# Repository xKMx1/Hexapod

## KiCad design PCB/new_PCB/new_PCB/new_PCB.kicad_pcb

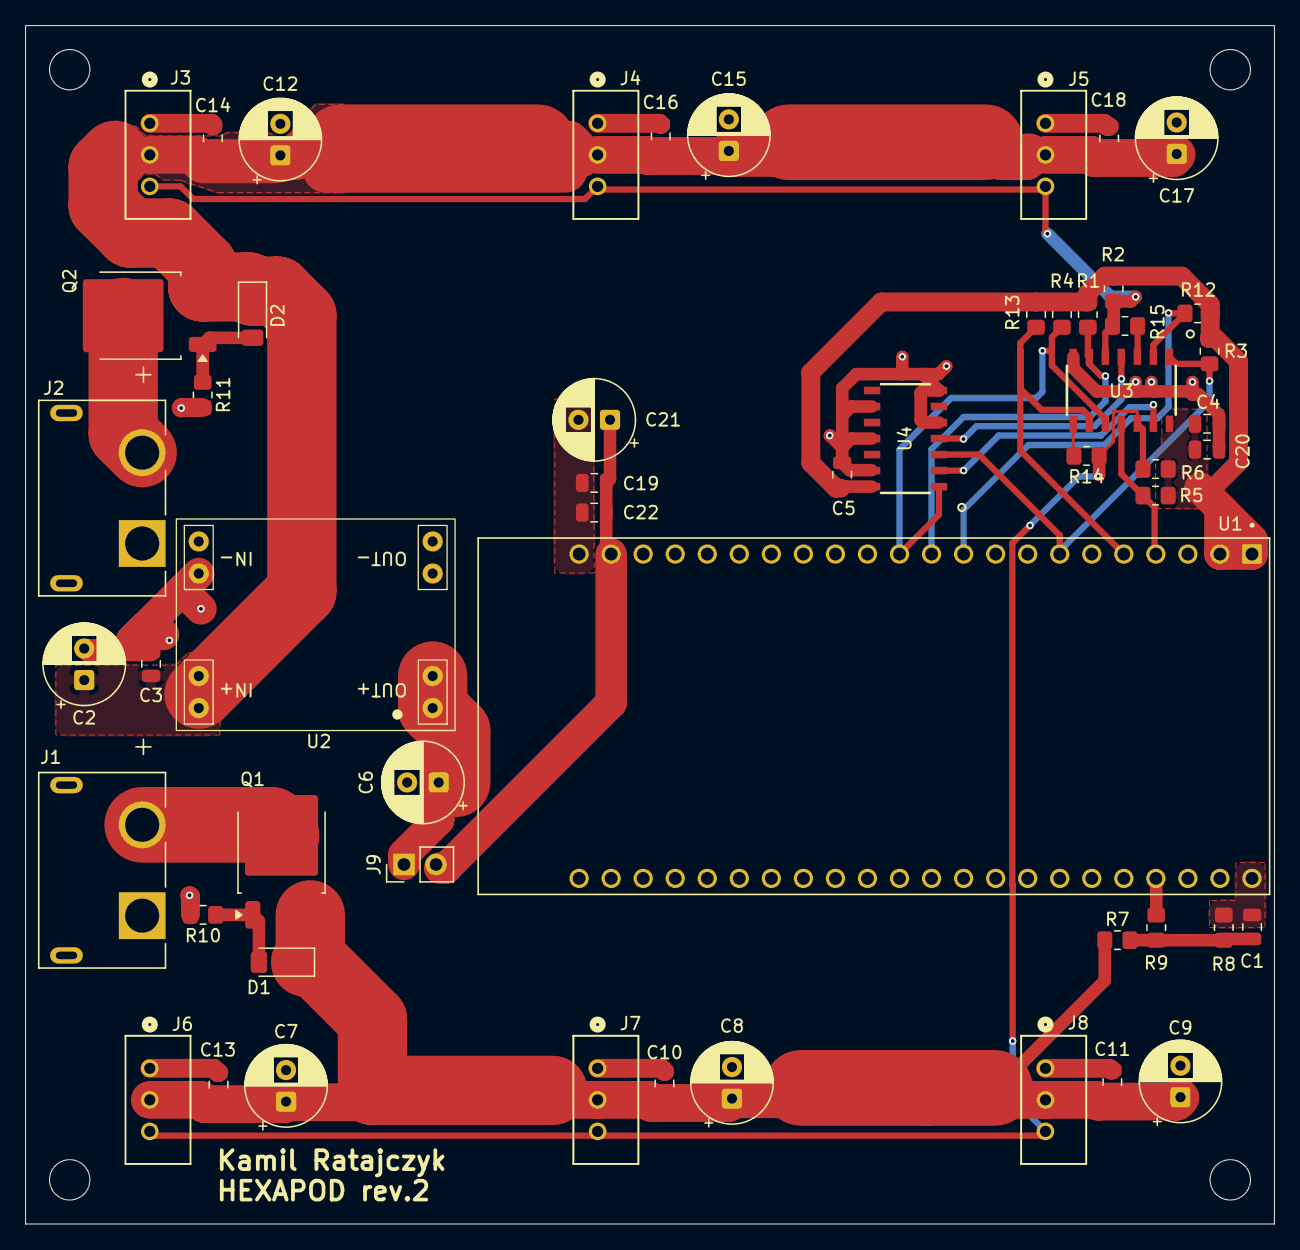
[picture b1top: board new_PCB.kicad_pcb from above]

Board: 2 copper layers, 99.0 x 95.0 mm, 58 parts (0 on the bottom side), 24 nets.

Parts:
C1, C3, C4, C5, C10, C11, C13, C14, C16, C18, C22: 100nF; C_0805_2012Metric
C2: 100uF; CP_Radial_D6.3mm_P2.50mm
C6: 22uF; CP_Radial_D6.3mm_P2.50mm
C7, C8, C9, C12, C15, C17, C21: 220uF; CP_Radial_D6.3mm_P2.50mm
C19, C20: 10uF; C_0805_2012Metric
D1, D2: BZV55B15; D_MiniMELF
H1, H2, H3, H4: MountingHole; MountingHole_3.2mm_M3_ISO14580
J1, J2: XT60PW-F; AMASS-XT60PW-F
J3, J4, J5, J6, J7, J8: MOLEX-Connector; CONN_22035035_MOL
J9: Conn_01x02; PinHeader_1x02_P2.54mm_Vertical
Q1, Q2: SUD50P04-08; TO-252-2
R1, R2, R3, R4, R5, R6, R10, R11, R12, R13: 10k; R_0805_2012Metric_Pad1.20x1.40mm_HandSolder
R7: 100k; R_0805_2012Metric_Pad1.20x1.40mm_HandSolder
R8: 22k; R_0805_2012Metric_Pad1.20x1.40mm_HandSolder
R9: 1k; R_0805_2012Metric_Pad1.20x1.40mm_HandSolder
R14, R15: 22R; R_0805_2012Metric_Pad1.20x1.40mm_HandSolder
U1: ESP32-S3-DEVKITC-1-N16R8V
U2: MP1584EN
U3: 74LVC125A1; SOT108-1
U4: 74LVC14A1; SOT108-1

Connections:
+3V3: C4.1, C5.1, C20.1, R1.1, R2.1, R3.1, R4.1, R5.1, R6.1, R12.1, R13.1, U1.J1_1 (+3V3), U1.J1_2 (+3V3), U3.14 (VCC), U4.14 (VCC)
+5V: C19.1, C21.1, C22.1, J9.2, U1.J1_21 (+5V)
/125_OUTPUT_RES_1: R15.1, U3.3 (1Y)
/125_OUTPUT_RES_2: R14.2, U3.8 (3Y)
/+5V_RAW: C6.1, J9.1, U2.1 (OUT+), U2.2 (OUT+)
/BAT_LVL: R9.2, U1.J3_4 (GPIO1)
/BAT_LVL_DIV: C1.1, R7.2, R8.1, R9.1
/Q1_GATE: D1.2 (A), Q1.1 (G), R10.1
/Q2_GATE: D2.2 (A), Q2.1 (G), R11.1
/RX1: R1.2, U1.J1_11 (GPIO18), U3.6 (2Y)
/RX2: R5.2, U1.J1_4 (GPIO4), U3.11 (4Y)
/RXEN1: U3.4 (2/OE), U4.4 (2Y)
/RXEN2: U3.13 (4/OE), U4.2 (1Y)
/SERVO_DATA1: J3.3, J4.3, J5.3, R2.2, R15.2, U3.5 (2A)
/SERVO_DATA2: J6.3, J7.3, J8.3, R6.2, R14.1, U3.12 (4A)
/TX1: R12.2, U1.J1_10 (GPIO17), U3.2 (1A)
/TX2: R13.2, U1.J1_5 (GPIO5), U3.9 (3A)
/TXEN1: R3.2, U1.J1_7 (GPIO7), U3.1 (1/OE), U4.3 (2A)
/TXEN2: R4.2, U1.J1_12 (GPIO8), U3.10 (3/OE), U4.1 (1A)
GND: C1.2, C2.2, C3.2, C4.2, C5.2, C6.2, C7.2, C8.2, C9.2, C10.2, C11.2, C12.2, C13.2, C14.2, C15.2, C16.2, C17.2, C18.2, C19.2, C20.2, C21.2, C22.2, J1.2 (N), J2.2 (N), J3.1, J4.1, J5.1, J6.1, J7.1, J8.1, R8.2, R10.2, R11.2, U1.J1_22 (GND), U1.J3_1 (GND), U1.J3_21 (GND), U1.J3_22 (GND), U2.3 (OUT-), U2.4 (OUT-), U2.5 (IN-), U2.6 (IN-), U3.7 (GND), U4.5 (3A), U4.7 (GND), U4.9 (4A), U4.11 (5A), U4.13 (6A)
VBAT_1: J1.1, Q1.2 (D)
VBAT_2: J2.1, Q2.2 (D)
VBUS_1: C7.1, C8.1, C9.1, C10.1, C11.1, C13.1, D1.1 (K), J6.2, J7.2, J8.2, Q1.3 (S), R7.1
VBUS_2: C2.1, C3.1, C12.1, C14.1, C15.1, C16.1, C17.1, C18.1, D2.1 (K), J3.2, J4.2, J5.2, Q2.3 (S), U2.7 (IN+), U2.8 (IN+)

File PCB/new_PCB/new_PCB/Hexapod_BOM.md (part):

# Hexapod carrier board: BOM and TME order list

Generated from `PCB/new_PCB/new_PCB/new_PCB.kicad_sch` (schematic saved 2026-09-12). Order quantities are for **1 board**, with a few spares on the small parts.

> **About the links:** every TME link points to a real product page. TME rate-limited the automated checks, so **current stock was not verified**. Check stock and price when you add each item to the basket. If a part is out of stock, the *Specs* column says what an equivalent must match.

---

## 1. Order from TME

| # | Ref | Part | Specs | TME code | Need | Order | Link |
|---|-----|------|-------|----------|-----:|------:|------|
| 1 | Q1, Q2 | Vishay **SUD50P04-08-GE3** | P-MOSFET, −40 V, −50 A, 8 mΩ, DPAK/TO-252 (1 = G, 2 = D/tab, 3 = S) | SUD50P04-08-GE3 | 2 | 3 | [TME](https://www.tme.eu/pl/details/sud50p04-08-ge3/) |
| 2 | U3 | Nexperia **74LVC125AD,118** | quad tri-state buffer, SO14 (SOT108-1) | 74LVC125AD.118 | 1 | 2 | [TME](https://www.tme.eu/pl/details/74lvc125ad.118/) |
| 3 | U4 | Nexperia **74LVC14AD,118** | hex Schmitt inverter, SO14 (SOT108-1) | 74LVC14AD.118 | 1 | 2 | [TME](https://www.tme.eu/pl/details/74lvc14ad.118/) |
| 4 | D1, D2 | Nexperia **BZV55-B15,115** | Zener 15 V ±2 %, 0.5 W, SOD80C (MiniMELF) | BZV55-B15.115 | 2 | 5 | [TME](https://www.tme.eu/pl/details/bzv55-b15.115/) |
| 5 | J3–J8 | Molex **22-03-5035** (Mini-SPOX) | 3-pin header, 2.5 mm pitch, straight, THT, 3 A. The header ROBOTIS specifies for the AX-12A | MX-5267-03A | 6 | 7 | [TME](https://www.tme.eu/pl/details/mx-5267-03a/) |
| 6 | C7, C8, C9, C12, C15, C17, C21 | Samxon **EKM227M1EE11RRSHP** | 220 µF / **25 V**, Ø6.3 × 11 mm, **2.5 mm pitch** | KM220/25 | 7 | 10 | [TME](https://www.tme.eu/pl/details/km220_25/) |
| 7 | C6 | Samwha **SD2A226M6L011PC** | 22 µF / 100 V, Ø6.3 × 11 mm, 2.5 mm pitch (see note D) | SD2A226M6L011PC | 1 | 2 | [TME](https://www.tme.eu/pl/details/sd2a226m6l011pc/) |
| 8 | C19, C20 | Samsung **CL21A106KAYNNNE** | 10 µF / 25 V, X5R, 0805 | CL21A106KAYNNNE | 2 | 5 | [TME](https://www.tme.eu/pl/details/cl21a106kaynnne/) |
| 9 | C1, C3, C4, C5, C10, C11, C13, C14, C16, C18, C22 | Walsin **0805B104K500CT** | 100 nF / 50 V, X7R, 0805 (the same part you bought before) | 0805B104K500CT | 11 | 20 | [TME](https://www.tme.eu/pl/details/0805b104k500ct/) |
| 10 | R14, R15 | Royalohm **0805S8J0220T5E** | 22 Ω, 5 %, 0805 (sold in packs of 100) | SMD0805-22R | 2 | 100 | [TME](https://www.tme.eu/pl/details/smd0805-22r/) |
| 11 | U1 socket | Connfly **DS1023-1\*40S21** | female socket 1 × 40, 2.54 mm, straight, THT. **Cut each strip to 22** (see note B) | ZL262-40SG | 2 × 22 | 2 | [TME](https://www.tme.eu/pl/details/zl262-40sg/) |
| 12 | J9 | Connfly **DS1021-1\*2SF11-B** | male pin header 1 × 2, 2.54 mm, straight, THT | ZL201-02G | 1 | 2 | [TME](https://www.tme.eu/pl/details/zl201-02g/) |
| 13 | J9 | Ninigi **JUMPER-H/R** | 2.54 mm jumper, lets you run without the switch on the bench | JUMPER-H/R | 1 | 2 | [TME](https://www.tme.eu/pl/details/jumper-h_r/) |

## 2. Off-board protection and switch (TME)

| # | Part | Specs | TME code | Order | Link |
|---|------|-------|----------|------:|------|
| 14 | MTA **UNIVAL 20A** blade fuse | ATO/ATC 19 mm, 20 A, 32 V DC | AMF-20A | 3 | [TME](https://www.tme.eu/pl/details/amf-20a/) |
| 15 | Littelfuse **0FHA0002ZXJ** inline fuse holder | ATO/ATC 19 mm, **30 A** holder, 12 AWG leads (~10 cm), 32 V | 0FHA0002ZXJ | 1 | [TME](https://www.tme.eu/pl/details/0fha0002zxj/) |
| 16 | Ninigi **KN3(C)-101A-A1** toggle switch | SPST ON-OFF, 10 A / 250 V AC, **M3 screw terminals**, panel hole **Ø12.2 mm**. In stock (3930 pcs, checked 2026-09-24). Replaces KS132 (TS-20/BL), which is out of stock | TSP101AA1 | 1 | [TME](https://www.tme.eu/pl/details/tsp101aa1/) |

- **Fuse holder:** put it in the battery **+** lead **before** the Y-splitter, so one fuse protects both VBUS branches.
- **Switch:** it only interrupts the ESP32's 5 V (J9 carries about 0.5 A), so this switch has plenty of margin. Connect it to J9 with a 2-wire lead ending in a female 2.54 mm (DuPont) connector. A female–female jumper cable cut in half works.

## 3. Already have (don't order)

| Ref | Part | Qty needed | You have |
|-----|------|-----------:|---------:|
| J1, J2 | AMASS **XT60PW-M** (see note A) | 2 | 3 |
| C2 | Samwha RD1V107M6L011BB, 100 µF / 35 V, Ø6.3 × 11 | 1 | 20 |
| R1–R6, R10–R13 | Royalohm 10 kΩ 1 % 0805 | 10 | 100 |
| R7 | Royalohm 100 kΩ 1 % 0805 | 1 | 100 |
| R8 | Royalohm 22 kΩ 0805 | 1 | 100 |
| R9 | Royalohm 1 kΩ 1 % 0805 | 1 | 100 |
| C (100 nF) | Walsin 0805B104K500CT | (11 total, see item 9) | 3 |
| U2 | MP1584EN module | 1 | 1 |
| U1 | ESP32-S3-DevKitC-1 N16R8V | 1 | 1 |
| — | ToolkitRC XT60 Y-splitter (1 male → 2 female) | 1 | 1 |
| — | Battery, external cables | — | yes |
| — | AOD407 P-MOSFET ×3 | **don't use** (note C) | 3 |

## 4. Notes. Read before assembling.

**A. XT60 gender.** Your Y-splitter has **female** outputs, so the board needs **male** connectors. The **XT60PW-M** you already have is correct, even though the schematic value and footprint are named "XT60PW-F". Pin spacing matches (7.2 mm). Before soldering, hold one against the board and check that its two side retention legs line up with the oval slots.

**B. ESP32 sockets.** TME doesn't sell a 22-pin female socket, so cut a 40-pin strip. Cut **through the 23rd pin position** with a fine saw or side cutters and file it flat; you lose that one position, which is why each 40-pin strip gives one 22-pin socket. Plug the devkit into both sockets while soldering them so they come out straight and parallel. This assumes your devkit has male pins already soldered on. If it doesn't, also order a 1 × 40 male strip (ZL201-40G) and cut two 22-pin pieces.

**C. AOD407 isn't suitable here.** Its datasheet gives R<sub>DS(on)</sub> ≤ 115 mΩ at −10 V and 50 °C/W junction-to-air. At about 4 A per branch that's ~1.8 W, roughly a 90 °C temperature rise in a DPAK on this board. The SUD50P04-08 (8 mΩ) dissipates ~0.13 W at the same current. Keep the AOD407s for low-current jobs.

**D. C6 alternative.** C6 (22 µF on the buck output) can be one of your spare **100 µF / 35 V** Samwha caps instead. Same footprint, and the extra bulk on a 5 V rail is harmless. If you do that, skip item 7.

**E. MP1584EN.** Set the output to **5.0 V** with a multimeter **before** you fit the module.

**F. Servo connectors.** Molex 22-03-5035 is the header ROBOTIS lists for the AX-12A (mating cable housing 50-37-5033, crimp 08-70-1039). Pinout: 1 = GND, 2 = VDD, 3 = DATA, which matches J3–J8 on the board.

**G. 100 nF stock.** TME's page for 0805B104K500CT showed conflicting stock info. If it's unavailable, any **100 nF / 50 V / X7R / 0805** works.

---

## 5. Full board BOM (for assembly)

| Ref | Value | Footprint | Qty |
|-----|-------|-----------|----:|
| C1, C3, C4, C5, C10, C11, C13, C14, C16, C18, C22 | 100 nF | 0805 | 11 |
| C2 | 100 µF | CP_Radial D6.3 P2.50 | 1 |
| C6 | 22 µF | CP_Radial D6.3 P2.50 | 1 |
| C7, C8, C9, C12, C15, C17, C21 | 220 µF | CP_Radial D6.3 P2.50 | 7 |
| C19, C20 | 10 µF | 0805 | 2 |
| D1, D2 | BZV55B15 | MiniMELF | 2 |
| J1, J2 | XT60 (fit XT60PW-M) | AMASS-XT60PW-F | 2 |
| J3–J8 | Molex 22-03-5035 | CONN_22035035_MOL | 6 |
| J9 | 1 × 2 header | PinHeader_1x02_P2.54 | 1 |
| Q1, Q2 | SUD50P04-08 | TO-252-2 | 2 |
| R1–R6, R10–R13 | 10 kΩ | 0805 | 10 |
| R7 | 100 kΩ | 0805 | 1 |
| R8 | 22 kΩ | 0805 | 1 |
| R9 | 1 kΩ | 0805 | 1 |
| R14, R15 | 22 Ω | 0805 | 2 |
| U1 | ESP32-S3-DevKitC-1 N16R8V (on 2 × 22 sockets) | — | 1 |
| U2 | MP1584EN module | — | 1 |
| U3 | 74LVC125A | SO14 | 1 |
| U4 | 74LVC14A | SO14 | 1 |

**Polarity:** electrolytics have pad 1 = + (square pad). BZV55: the cathode band goes toward the VBUS side (pin 1 = K).



Numer pozycji
Symbol TME
Symbol Klienta
Cena brutto
Ilość zamówiona
Wartość pozycji brutto
% VAT
Numer oferty
Dostawa kompletna pozycji
Waga
Opcje
1

SUD50P04-08-GE3
9.594 PLN
3
szt
28.78 PLN
23 %

1.22 g

3

BZV55-B15.115
0.461 PLN
5
szt
2.31 PLN
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
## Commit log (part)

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2024-01-22 Add first version of pcb scheamtics without power section
2024-01-24 Add 1st version of board schematics and pcb layout
2024-01-26 full schematics and routed pcb
2024-02-18 Add first version of 3d parts
2024-02-19 Update 3d files
2024-02-21 Update 3D models
2024-02-21 Add code project
2024-02-21 Add new leg part
2024-02-21 txt
    pzdr
2024-02-25 update code
2024-02-25 add new schematics
2024-02-25 fix bug
2024-02-29 Add gcode files for 3d parts
2024-02-29 Add PCB schematics
2024-02-29 Add PCB 1st version
2024-02-29 Add gitignore
2024-02-29 Finish first version of the PCB
2024-03-02 Delete 3DPrinterFiles/all_6h40m.gcode
    Delete .gcode file from repo
2024-03-18 Add basic base 3d model
2024-03-18 Update base 3d model
2024-03-18 Add mounting holes to base model and update assembly
2024-03-18 Slight changes to base model
2024-03-18 Change hole sizes
2024-03-20 Change base 3d model
2024-03-28 add mounting holes to pcb and generate gerber files
2024-03-28 Tidy up the directory
2024-04-02 Update pcb with manufacturer logos
2024-04-05 change pcb
2026-03-25 Modify .gitignore and webots project
2026-03-25 Stop tracking files covered by .gitignore
2026-03-26 Prepare hexapod model for rl
2026-03-26 add corret path in runtime.ini and basic webots constants in hexapod_env
2026-03-26 Add testing code to hexapod_env' q
2026-03-27 Add basic functions to hexapod_env
2026-03-27 Add working random actions mode, with action and reset
2026-03-27 Add code to start training
2026-03-27 Fix repo push
2026-03-31 Change hexapod model to better fit the real one, and change some moving functions in basic controller
2026-03-31 Add small tweaks in robot model and learning script
2026-06-14 Fix reward function
2026-06-18 Fix setup and add new Kicad pcb project
2026-06-20 Add full duplex -> half duplex logic and input power
2026-06-21 Add servo connectors and 3d models
2026-06-21 Add first quick version of PCB routing
